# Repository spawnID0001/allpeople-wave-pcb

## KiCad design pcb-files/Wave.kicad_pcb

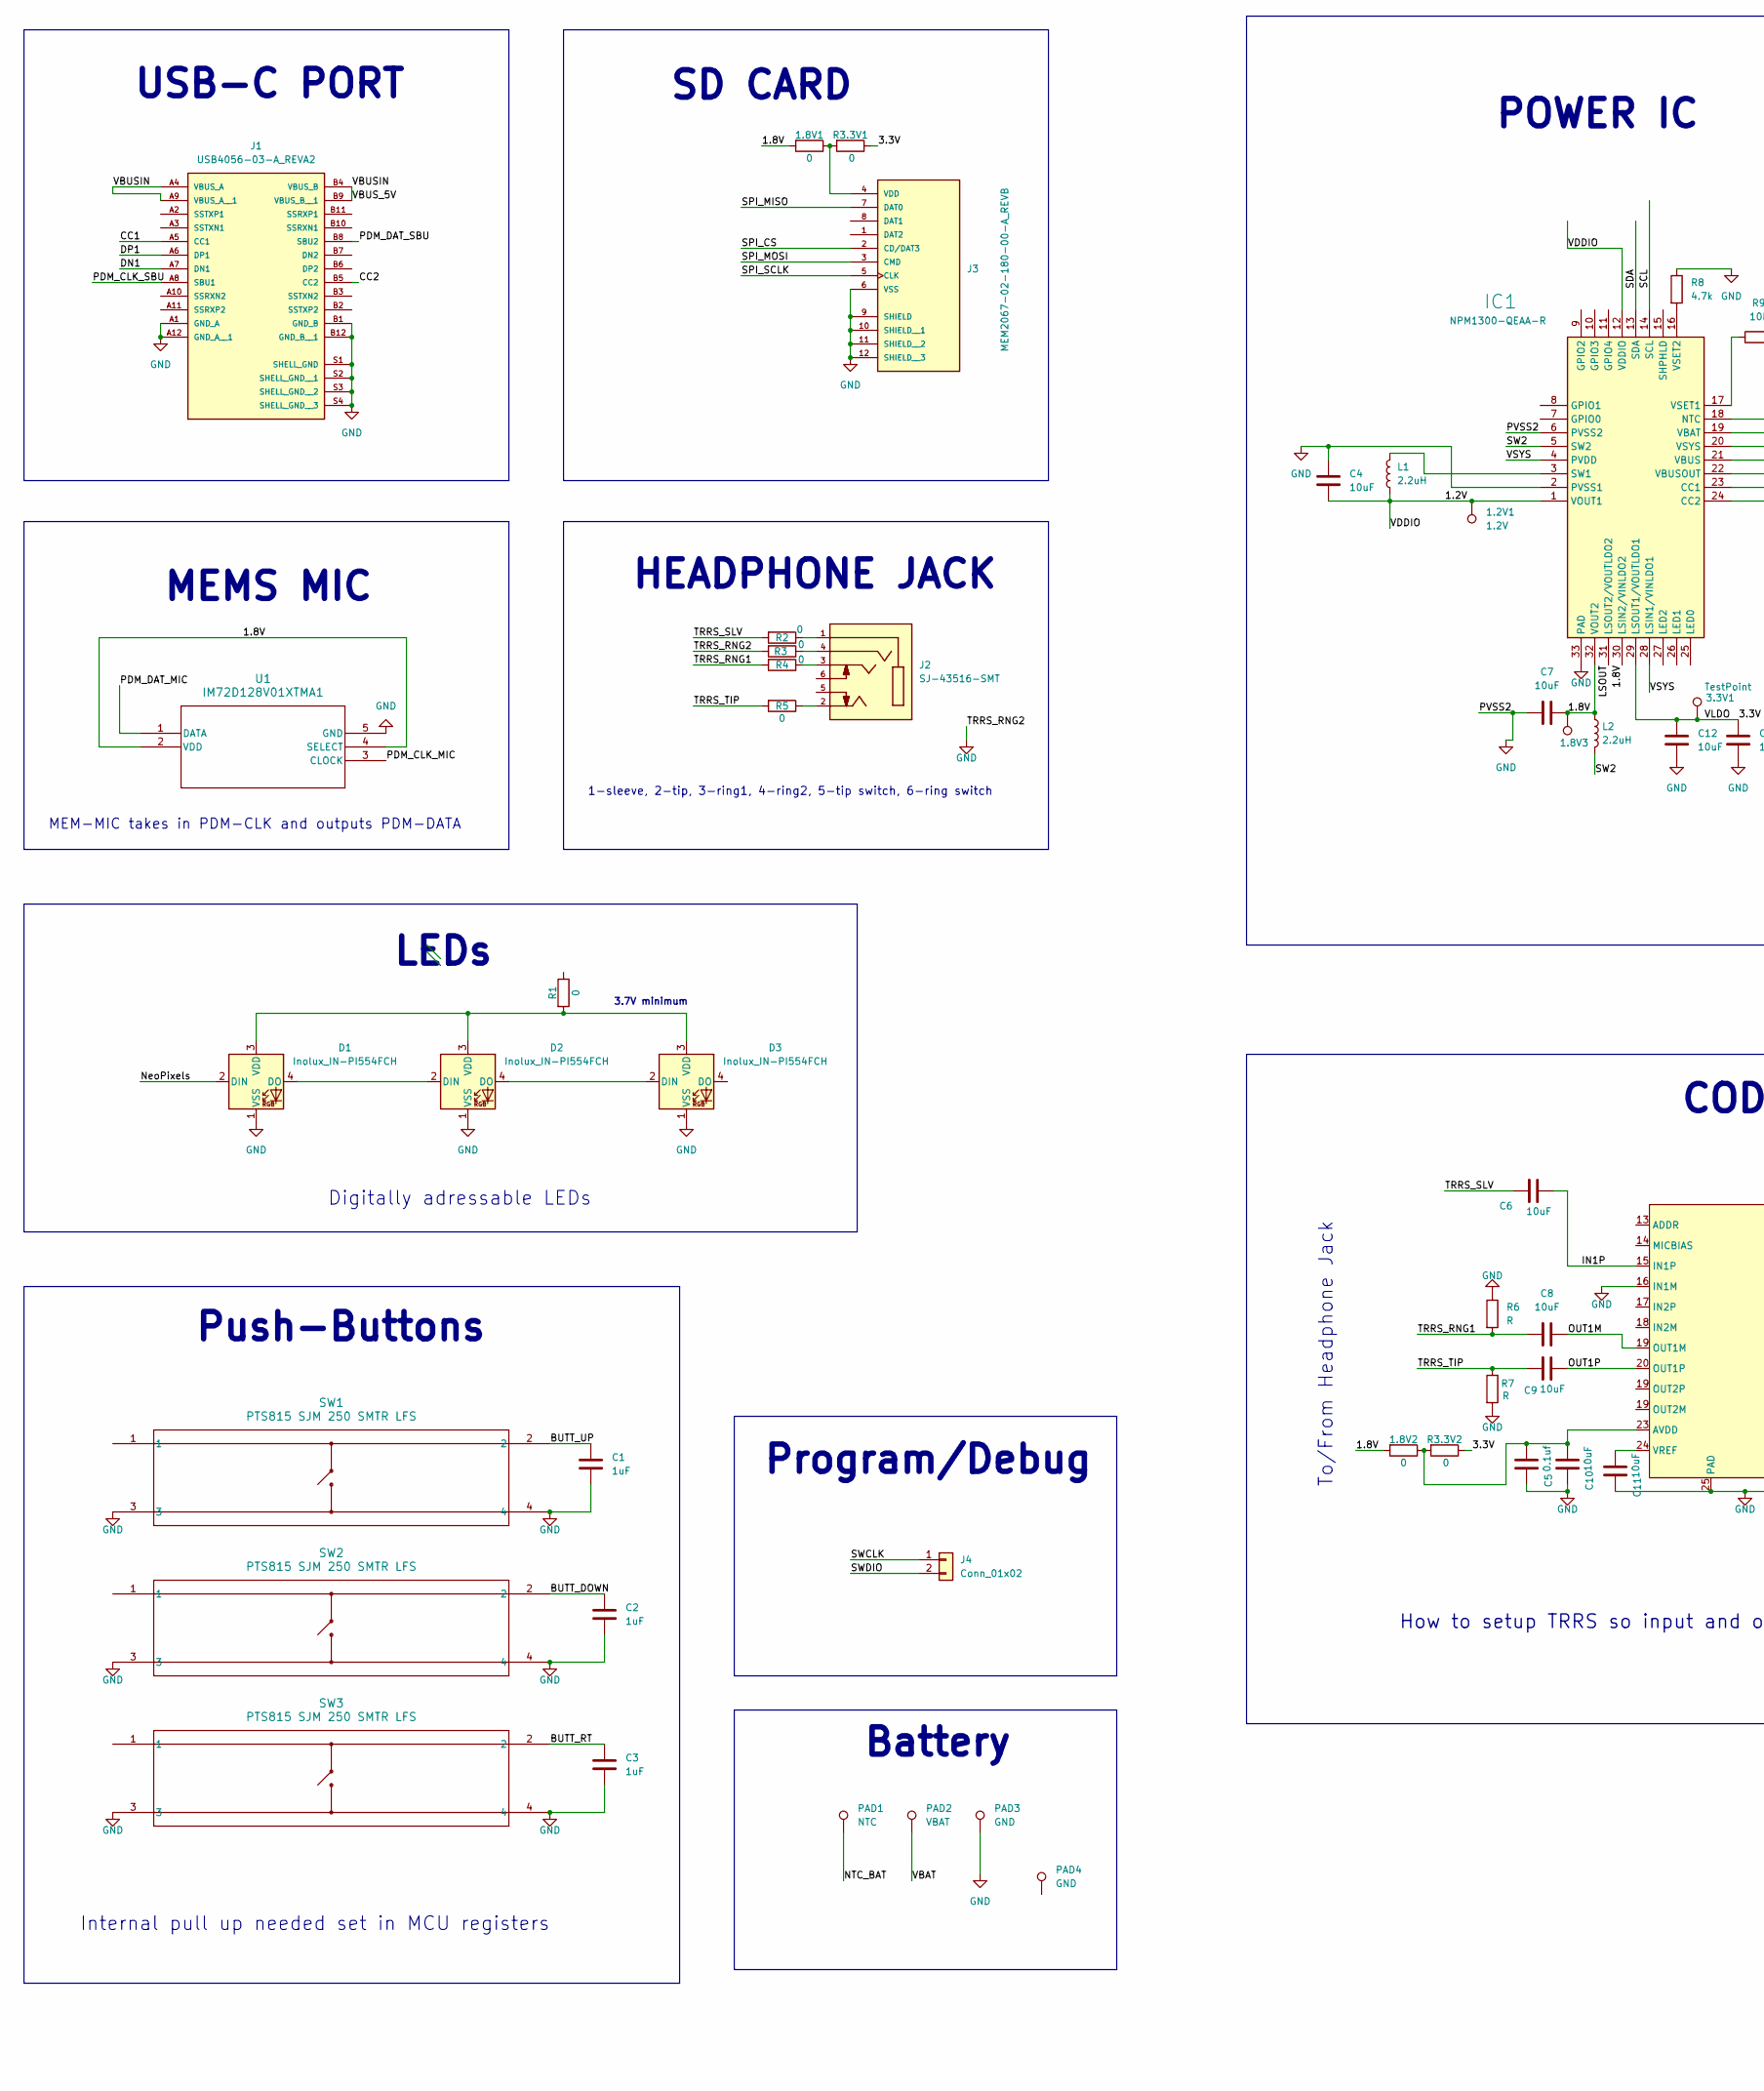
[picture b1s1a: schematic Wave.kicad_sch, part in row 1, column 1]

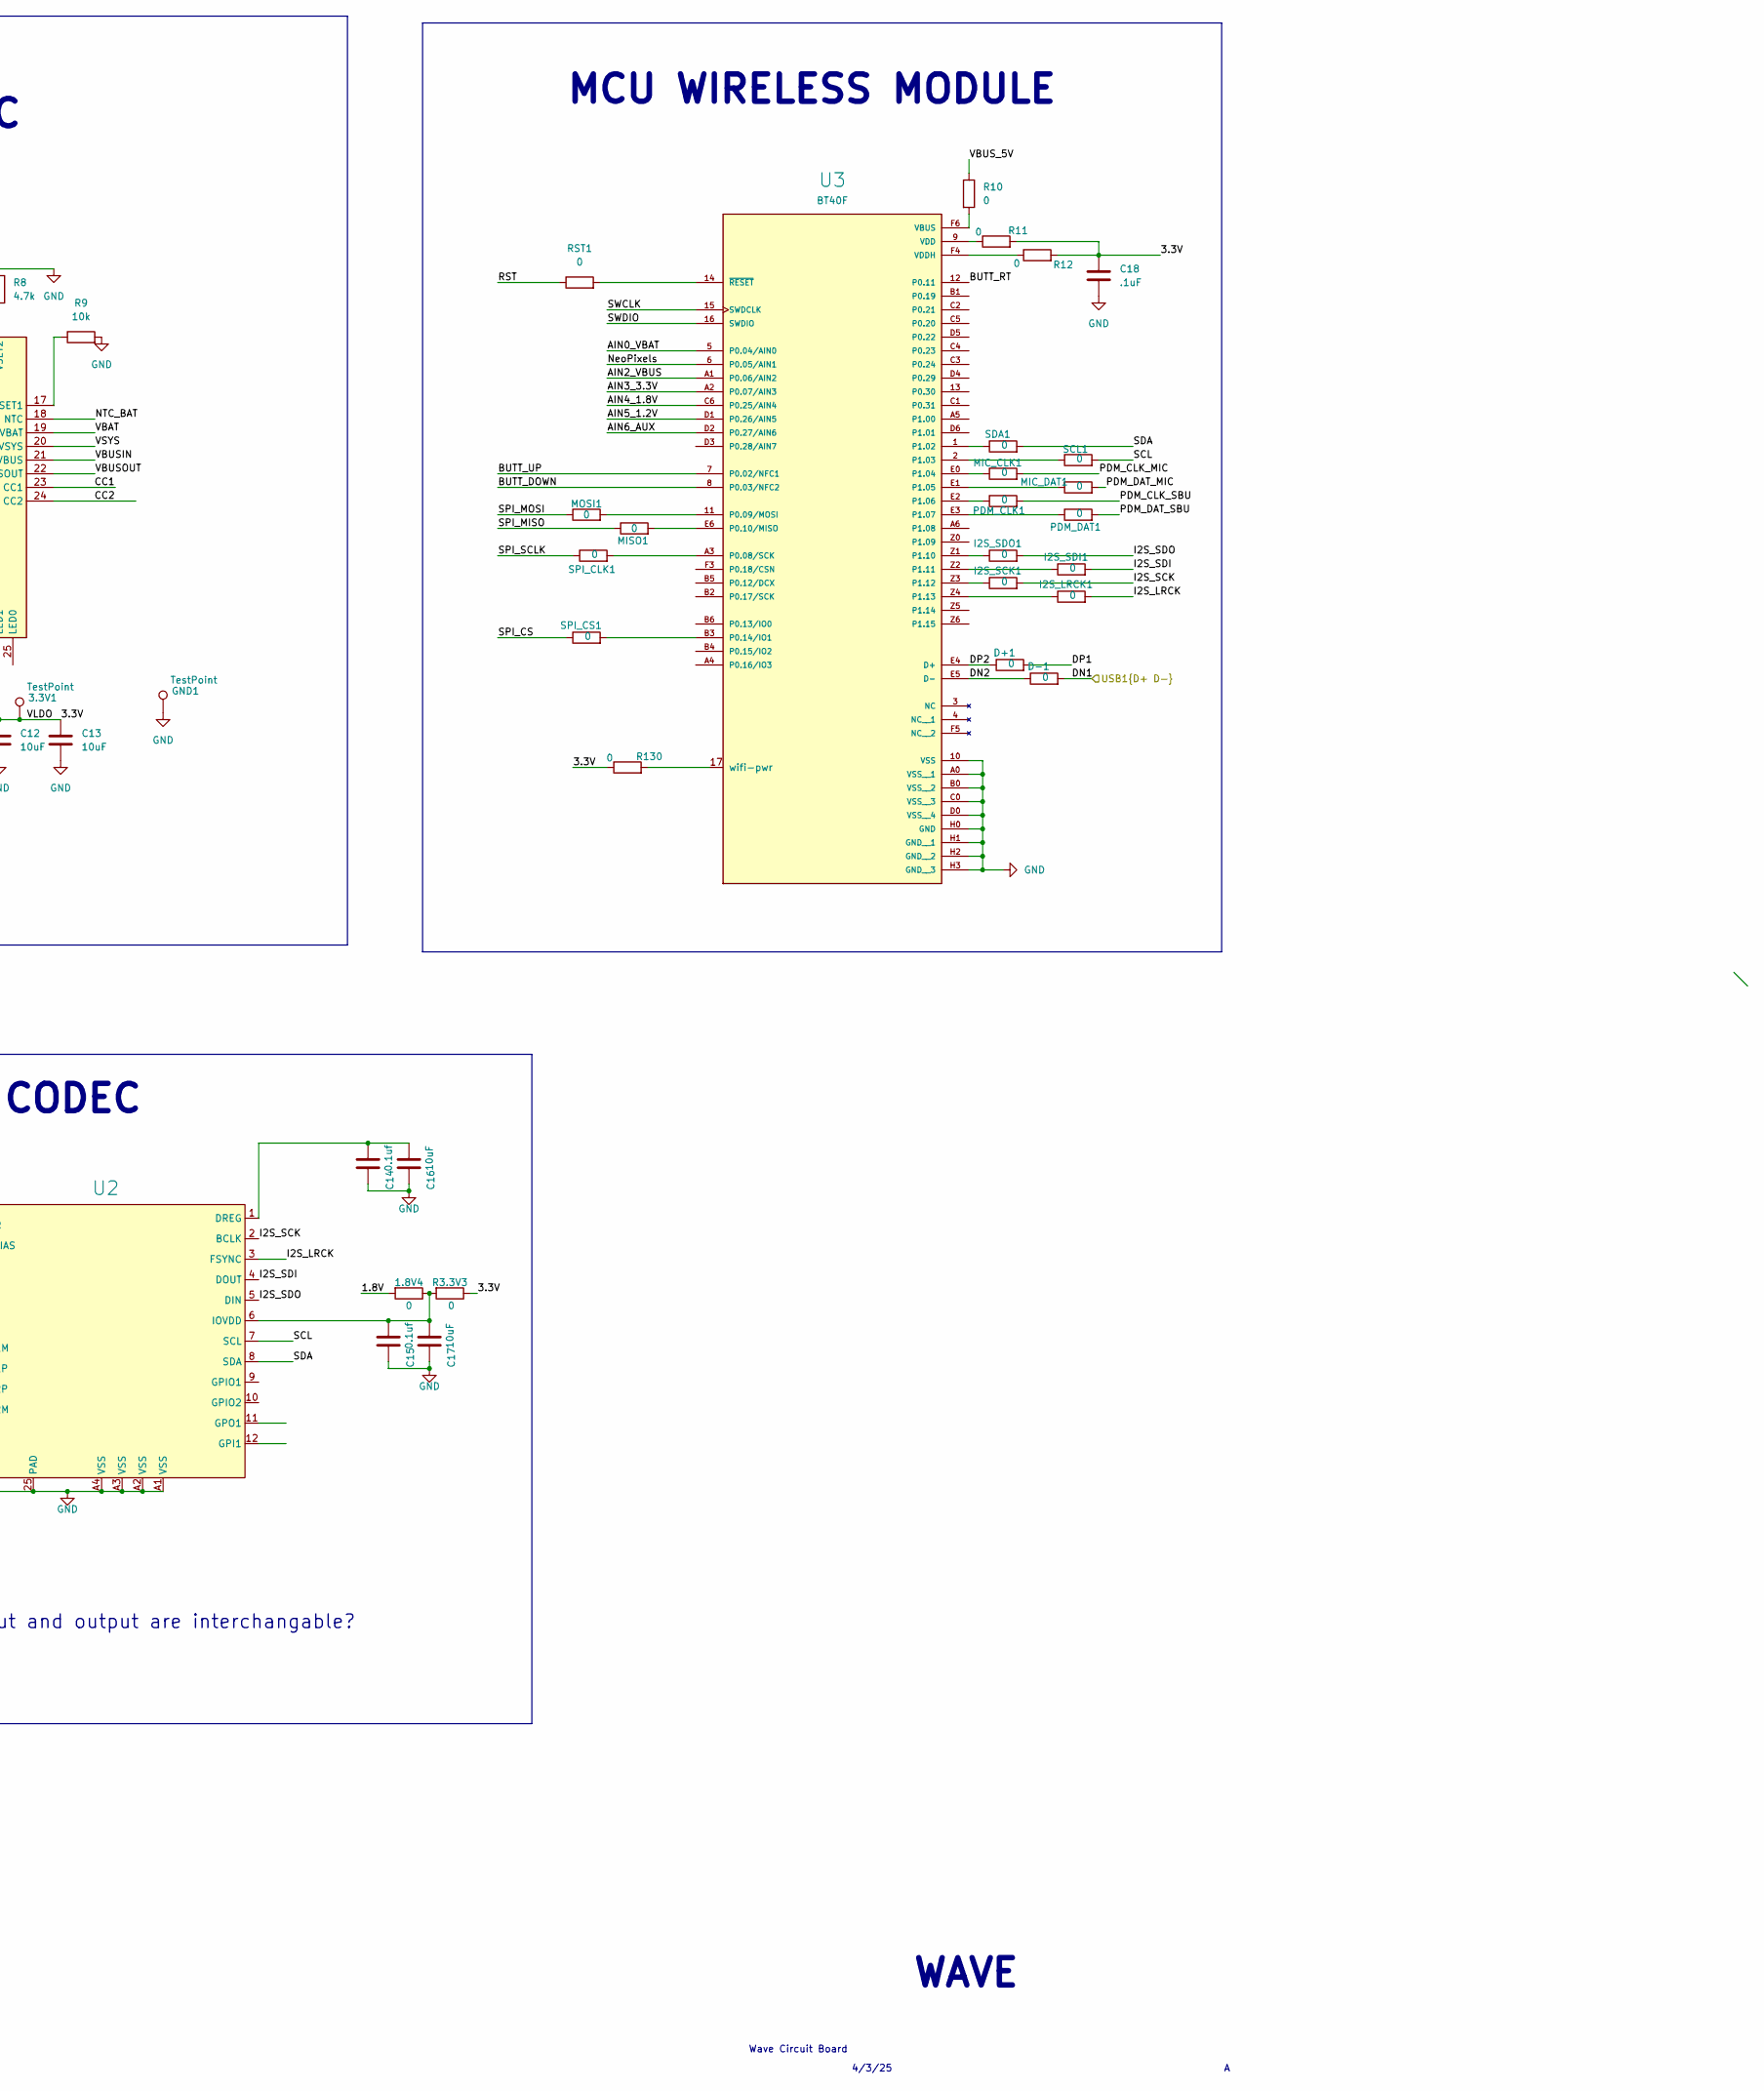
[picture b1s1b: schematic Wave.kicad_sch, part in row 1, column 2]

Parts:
1.2V1: 1.2V; TestPoint_Pad_1.0x1.0mm
1.8V1, 1.8V2, 1.8V4: 0; R_0402_1005Metric
1.8V3: 1.8V; TestPoint_Pad_1.0x1.0mm
3.3V1: TestPoint; TestPoint_Pad_1.0x1.0mm
C1, C2, C3: 1uF; C_0402_1005Metric_Pad0.74x0.62mm_HandSolder
C4, C6, C7, C8, C9, C10, C11, C12, C13, C16, C17: 10uF; C_0402_1005Metric_Pad0.74x0.62mm_HandSolder
C5, C14, C15: 0.1uf; C_0402_1005Metric_Pad0.74x0.62mm_HandSolder
C18: .1uF; C_0402_1005Metric_Pad0.74x0.62mm_HandSolder
D1, D2, D3: Inolux_IN-PI554FCH; LED_Inolux_IN-PI554FCH_PLCC4_5.0x5.0mm_P3.2mm
D+1: 0; R_0402_1005Metric
D-1: 0; R_0402_1005Metric
GND1: TestPoint; TestPoint_Pad_1.0x1.0mm
I2S_LRCK1, I2S_SCK1, I2S_SDI1, I2S_SDO1: 0; R_0402_1005Metric
IC1: NPM1300-QEAA-R; QFN50P500X500X90-33N; Manufacturer_Part_Number NPM1300-QEAA-R
J1: USB4056-03-A_REVA2; GCT_USB4056-03-A_REVA2; PARTREV A2
J2: SJ-43516-SMT; CUI_SJ-43516-SMT; PART_REV 1.02; DigiKey_Part_Number CP-43516SJTR-ND
J3: MEM2067-02-180-00-A_REVB; GCT_MEM2067-02-180-00-A_REVB
J4: Conn_01x02; PinHeader_1x02_P1.00mm_Vertical; Part Number 1-0201FBV0T
L1, L2: 2.2uH; L_0402_1005Metric
MIC_CLK1: 0; R_0402_1005Metric
MIC_DAT1: 0; R_0402_1005Metric
MISO1: 0; R_0402_1005Metric
MOSI1: 0; R_0402_1005Metric
PAD1: NTC; TestPoint_Pad_D2.0mm
PAD2: VBAT; TestPoint_Pad_D2.0mm
PAD3: GND; TestPoint_Pad_D2.0mm
PAD4: GND; Battery_CR1225
PDM_CLK1: 0; R_0402_1005Metric
PDM_DAT1: 0; R_0402_1005Metric
R1, R2, R3, R3.3V1, R3.3V2, R3.3V3, R4, R5, R10, R11, R12, R130: 0; R_0402_1005Metric
R6, R7: R; R_0402_1005Metric
R8: 4.7k; R_0402_1005Metric
R9: 10k; R_0402_1005Metric
RST1: 0; R_0402_1005Metric
SCL1: 0; R_0402_1005Metric
SDA1: 0; R_0402_1005Metric
SPI_CLK1: 0; R_0402_1005Metric
SPI_CS1: 0; R_0402_1005Metric
SW1, SW2, SW3: PTS815 SJM 250 SMTR LFS; SW4_PTS815 SJM 250 SMTR LFS_CNK
U1: IM72D128V01XTMA1; PG-LLGA-5-3_INF
U2: WAVE_CODEC
U3: BT40F; XCVR_BT40F; PARTREV 1.01

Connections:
/1.2V: 1.2V1.1, C4.2, IC1.1 (VOUT1), IC1.12 (VDDIO), L1.1
/1.8V: 1.8V1.2, 1.8V2.2, 1.8V3.1, 1.8V4.2, C7.2, IC1.30 (LSIN2/VINLDO2), IC1.32 (VOUT2), L2.1, U1.2 (VDD), U1.4 (SELECT)
/3.3V: 3.3V1.1, C12.2, C13.2, C18.1, IC1.29 (LSOUT1/VOUTLDO1), R3.3V1.1, R3.3V2.1, R3.3V3.1, R11.2, R12.2, R130.1
/AIN0_VBAT: U3.5 (P0.04/AIN0)
/AIN2_VBUS: U3.A1 (P0.06/AIN2)
/AIN3_3.3V: U3.A2 (P0.07/AIN3)
/AIN4_1.8V: U3.C6 (P0.25/AIN4)
/AIN5_1.2V: U3.D1 (P0.26/AIN5)
/AIN6_AUX: U3.D2 (P0.27/AIN6)
/BUTT_DOWN: C2.1, SW2.2, U3.8 (P0.03/NFC2)
/BUTT_RT: C3.1, SW3.2, U3.12 (P0.11)
/BUTT_UP: C1.1, SW1.2, U3.7 (P0.02/NFC1)
/CC1: IC1.23 (CC1), J1.A5 (CC1)
/CC2: IC1.24 (CC2), J1.B5 (CC2)
/DN1: D-1.2, J1.A7 (DN1)
/DN2: D-1.1, U3.E5 (D-)
/DP1: D+1.2, J1.A6 (DP1)
/DP2: D+1.1, U3.E4 (D+)
/I2S_LRCK: I2S_LRCK1.2, U2.3 (FSYNC)
/I2S_SCK: I2S_SCK1.2, U2.2 (BCLK)
/I2S_SDI: I2S_SDI1.2, U2.4 (DOUT)
/I2S_SDO: I2S_SDO1.2, U2.5 (DIN)
/IN1P: C6.2, U2.15 (IN1P)
/LSOUT: IC1.31 (LSOUT2/VOUTLDO2)
/NTC_BAT: IC1.18 (NTC), PAD1.1; also elsewhere on the board
/NeoPixels: D1.2 (DIN), U3.6 (P0.05/AIN1)
/OUT1M: C8.2, U2.19 (OUT1M)
/OUT1P: C9.2, U2.20 (OUT1P)
/PDM_CLK_MIC: MIC_CLK1.2, U1.3 (CLOCK)
/PDM_CLK_SBU: J1.A8 (SBU1), PDM_CLK1.2
/PDM_DAT_MIC: MIC_DAT1.2, U1.1 (DATA)
/PDM_DAT_SBU: J1.B8 (SBU2), PDM_DAT1.2
/RST: RST1.1
/SCL: IC1.14 (SCL), SCL1.2, U2.7 (SCL)
/SDA: IC1.13 (SDA), SDA1.2, U2.8 (SDA)
/SPI_CS: J3.2 (CD/DAT3), SPI_CS1.1
/SPI_MISO: J3.7 (DAT0), MISO1.1
/SPI_MOSI: J3.3 (CMD), MOSI1.1
/SPI_SCLK: J3.5 (CLK), SPI_CLK1.1
/SW2: IC1.5 (SW2), L2.2
/SWCLK: J4.1, U3.15 (SWDCLK)
/SWDIO: J4.2, U3.16 (SWDIO)
/TRRS_RNG1: C8.1, R4.2, R6.2
/TRRS_SLV: C6.1, R2.2; also elsewhere on the board
/TRRS_TIP: C9.1, R5.2, R7.1
/VBAT: IC1.19 (VBAT), PAD2.1; also elsewhere on the board
/VBUSIN: IC1.21 (VBUS), J1.A4 (VBUS_A), J1.A9 (VBUS_A__1), J1.B4 (VBUS_B), J1.B9 (VBUS_B__1), R10.1
/VBUSOUT: IC1.22 (VBUSOUT)
/VSYS: IC1.4 (PVDD), IC1.20 (VSYS), IC1.28 (LSIN1/VINLDO1)
GND: C1.2, C2.2, C3.2, C4.1, C5.1, C7.1, C10.1, C11.1, C12.1, C13.1, C14.1, C15.1, C16.1, C17.1, C18.2, D1.1 (VSS), D2.1 (VSS), D3.1 (VSS), GND1.1, IC1.2 (PVSS1), IC1.6 (PVSS2), IC1.33 (PAD), J1.A1 (GND_A), J1.A12 (GND_A__1), J1.B1 (GND_B), J1.B12 (GND_B__1), J1.S1 (SHELL_GND), J1.S2 (SHELL_GND__1), J1.S3 (SHELL_GND__2), J1.S4 (SHELL_GND__3), J3.6 (VSS), J3.9 (SHIELD), J3.10 (SHIELD__1), J3.11 (SHIELD__2), J3.12 (SHIELD__3), PAD3.1, R3.2, R6.1, R7.2, R8.1, R9.2, SW1.3, SW1.4, SW2.3, SW2.4, SW3.3, SW3.4, U1.5 (GND), U2.16 (IN1M), U2.25 (PAD), U2.A1 (VSS), U2.A2 (VSS), U2.A3 (VSS), U2.A4 (VSS), U3.10 (VSS), U3.A0 (VSS__1), U3.B0 (VSS__2), U3.C0 (VSS__3), U3.D0 (VSS__4), U3.H0 (GND), U3.H1 (GND__1), U3.H2 (GND__2), U3.H3 (GND__3); also elsewhere on the board
unnamed: D1.4 (DO), D2.2 (DIN)
unnamed: D1.3 (VDD), D2.3 (VDD), D3.3 (VDD), R1.2
unnamed: D2.4 (DO), D3.2 (DIN)
unnamed: IC1.3 (SW1), L1.2
unnamed: IC1.17 (VSET1), R9.1
unnamed: IC1.16 (VSET2), R8.2
unnamed 56: J2.1, R2.1; also elsewhere on the board
unnamed: J2.2, R5.1
unnamed: J2.3, R4.1
unnamed: J2.4, R3.1
unnamed: 1.8V1.1, J3.4 (VDD), R3.3V1.2
unnamed: 1.8V2.1, C5.2, C10.2, R3.3V2.2, U2.23 (AVDD)
unnamed: C14.2, C16.2, U2.1 (DREG)
unnamed: 1.8V4.1, C15.2, C17.2, R3.3V3.2, U2.6 (IOVDD)
unnamed: C11.2, U2.24 (VREF)
unnamed: SPI_CLK1.2, U3.A3 (P0.08/SCK)
unnamed: MOSI1.2, U3.11 (P0.09/MOSI)
unnamed: MISO1.2, U3.E6 (P0.10/MISO)
unnamed: SPI_CS1.2, U3.B3 (P0.14/IO1)
unnamed: SDA1.1, U3.1 (P1.02)
unnamed: SCL1.1, U3.2 (P1.03)
unnamed: MIC_CLK1.1, U3.E0 (P1.04)
unnamed: MIC_DAT1.1, U3.E1 (P1.05)
unnamed: PDM_CLK1.1, U3.E2 (P1.06)
unnamed: PDM_DAT1.1, U3.E3 (P1.07)
unnamed: I2S_SDO1.1, U3.Z1 (P1.10)
unnamed: I2S_SDI1.1, U3.Z2 (P1.11)
unnamed: I2S_SCK1.1, U3.Z3 (P1.12)
unnamed: I2S_LRCK1.1, U3.Z4 (P1.13)
unnamed: R10.2, U3.F6 (VBUS)
unnamed: R11.1, U3.9 (VDD)
unnamed: R12.1, U3.F4 (VDDH)
unnamed: R130.2, U3.17 (wifi-pwr)
unnamed: RST1.2, U3.14 (~RESET)

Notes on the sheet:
4/3/25
Wave Circuit Board
MEM-MIC takes in PDM-CLK and outputs PDM-DATA
How to setup TRRS so input and output are interchangable?
SD CARD
Push-Buttons
Battery
3.7V minimum
USB-C PORT
Internal pull up needed set in MCU registers
To/From Headphone Jack
POWER IC
Digitally adressable LEDs
1-sleeve, 2-tip, 3-ring1, 4-ring2, 5-tip switch, 6-ring switch
HEADPHONE JACK
MCU WIRELESS MODULE
MEMS MIC
Program/Debug
WAVE
LEDs
CODEC

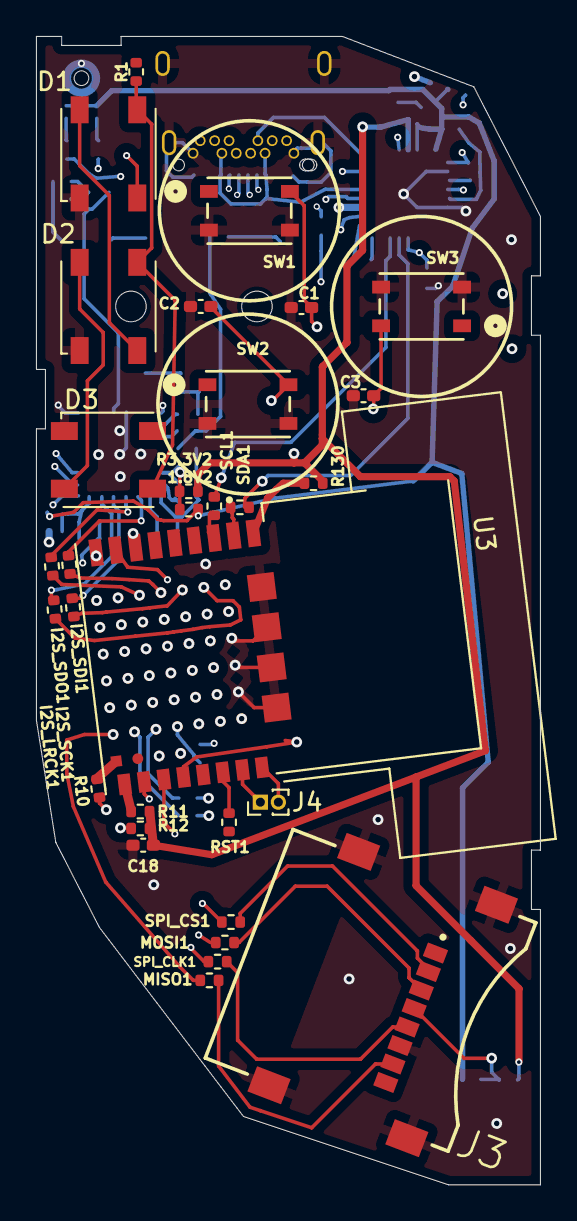
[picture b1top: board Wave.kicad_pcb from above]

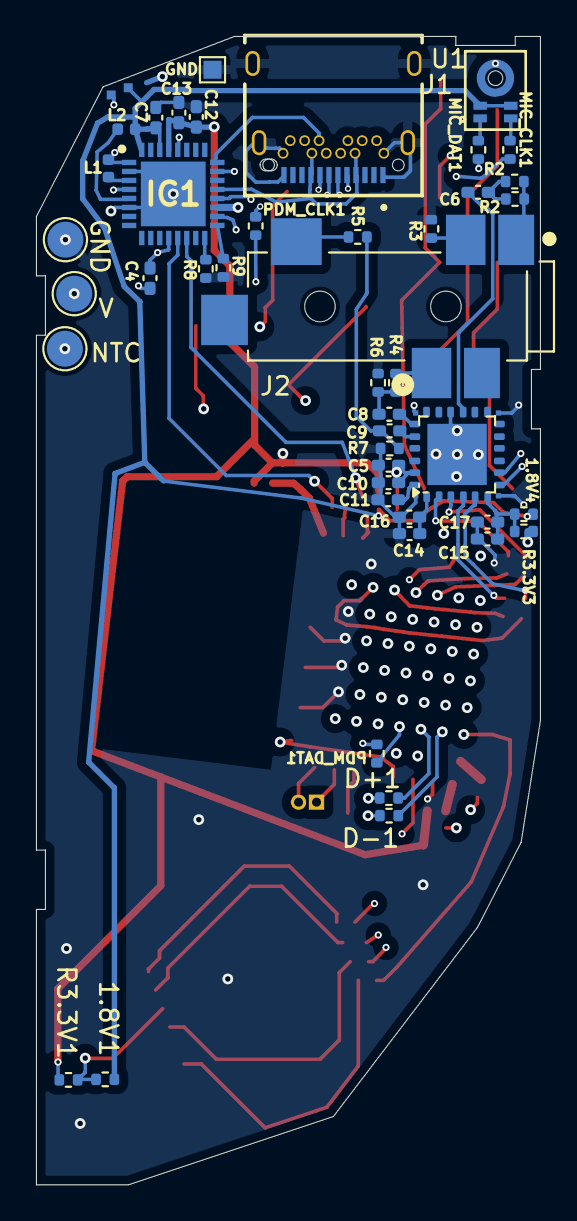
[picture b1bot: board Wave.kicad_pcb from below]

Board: 4 copper layers, 28.0 x 63.8 mm, 78 parts (47 on the bottom side), 75 nets.

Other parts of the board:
GND: GND; TestPoint_Pad_D2.0mm
GND#2: TestPoint; TestPoint_Pad_1.0x1.0mm
NTC: NTC; TestPoint_Pad_D2.0mm
R2#2: 0; R_0402_1005Metric
V: VBAT; TestPoint_Pad_D2.0mm

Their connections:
/NTC_BAT: NTC.1; also elsewhere on the board
/TRRS_SLV: R2#2.2; also elsewhere on the board
/VBAT: V.1; also elsewhere on the board
GND: GND.1, GND#2.1; also elsewhere on the board
unnamed 56: R2#2.1; also elsewhere on the board

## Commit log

2025-03-04 Added .gitkeep files to establish folder structure on repo
2025-03-12 New Sch Doc with pin 17 for wifi module
2025-04-07 Layout V1
    First Layout of Wave v1
2025-05-11 Silkscreen update
    Updated Silkscreen
